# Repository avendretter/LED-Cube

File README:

LED-Cube
Hi und herzlich willkommen.

Hier stelle ich nun meinen Code euch zur Verfügung. 

VIEL SPAß DAMIT =)

wünscht,

Avendretter

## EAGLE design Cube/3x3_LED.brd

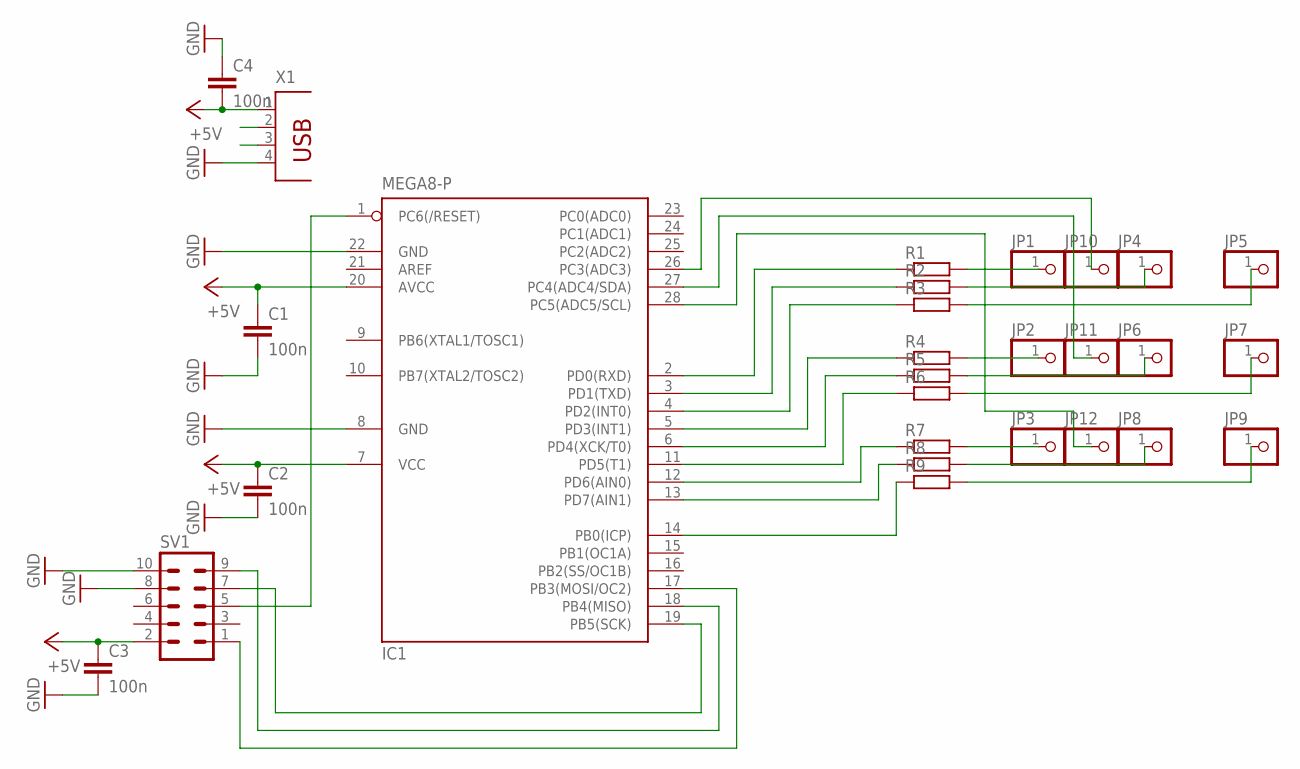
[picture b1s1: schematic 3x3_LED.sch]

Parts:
C1, C2, C3, C4: 100n; C025-024X044
IC1: MEGA8-P; DIL28-3
JP1, JP2, JP3, JP4, JP5, JP6, JP7, JP8, JP9, JP10, JP11, JP12: PINHD-1X1; 1X01
R1, R2, R3, R4, R5, R6, R7, R8, R9: R-EU_0207/12; 0207/12
SV1: ML10
X1: PN61729

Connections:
+5V: C1.1, C2.1, C3.1, C4.2, IC1.7 (VCC), IC1.20 (AVCC), SV1.2, X1.1
GND: C1.2, C2.2, C3.2, C4.1, IC1.8 (GND), IC1.22 (GND), SV1.8, SV1.10, X1.4
unnamed: JP1.1, R1.2
unnamed: JP4.1, R2.2
unnamed: JP5.1, R3.2
unnamed: JP2.1, R4.2
unnamed: JP6.1, R5.2
unnamed: JP7.1, R6.2
unnamed: JP3.1, R7.2
unnamed: JP8.1, R8.2
unnamed: JP9.1, R9.2
unnamed: IC1.2 (PD0(RXD)), R1.1
unnamed: IC1.3 (PD1(TXD)), R2.1
unnamed: IC1.4 (PD2(INT0)), R3.1
unnamed: IC1.5 (PD3(INT1)), R4.1
unnamed: IC1.6 (PD4(XCK/T0)), R5.1
unnamed: IC1.11 (PD5(T1)), R6.1
unnamed: IC1.12 (PD6(AIN0)), R7.1
unnamed: IC1.13 (PD7(AIN1)), R8.1
unnamed: IC1.14 (PB0(ICP)), R9.1
unnamed: IC1.26 (PC3(ADC3)), JP10.1
unnamed: IC1.27 (PC4(ADC4/SDA)), JP11.1
unnamed: IC1.28 (PC5(ADC5/SCL)), JP12.1
unnamed: IC1.17 (PB3(MOSI/OC2)), SV1.1
unnamed: IC1.19 (PB5(SCK)), SV1.7
unnamed: IC1.1 (PC6(/RESET)), SV1.5
unnamed: IC1.18 (PB4(MISO)), SV1.9

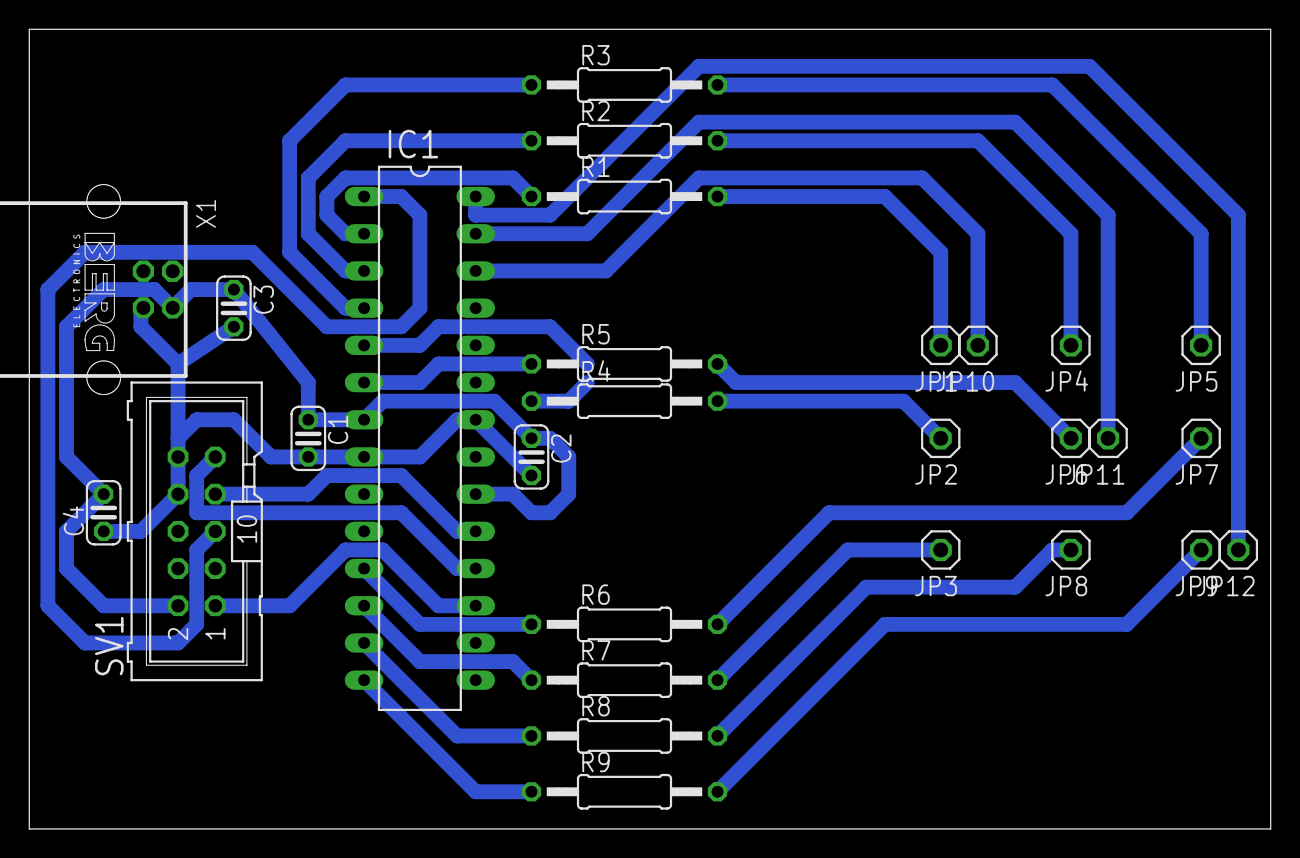
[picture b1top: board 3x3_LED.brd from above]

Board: 2 copper layers, 84.8 x 54.6 mm, 28 parts (0 on the bottom side), 27 nets.

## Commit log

2012-03-29 Hier meine Main-Datei
2012-03-29 update 29.3.12,22:51
2012-03-29 hier noch nen paar Codes
2012-03-29 Readme update
2012-03-29 README-Datei erstellt
2012-03-29 README
2012-03-30 update LED leutanordnung
2016-03-17 test
